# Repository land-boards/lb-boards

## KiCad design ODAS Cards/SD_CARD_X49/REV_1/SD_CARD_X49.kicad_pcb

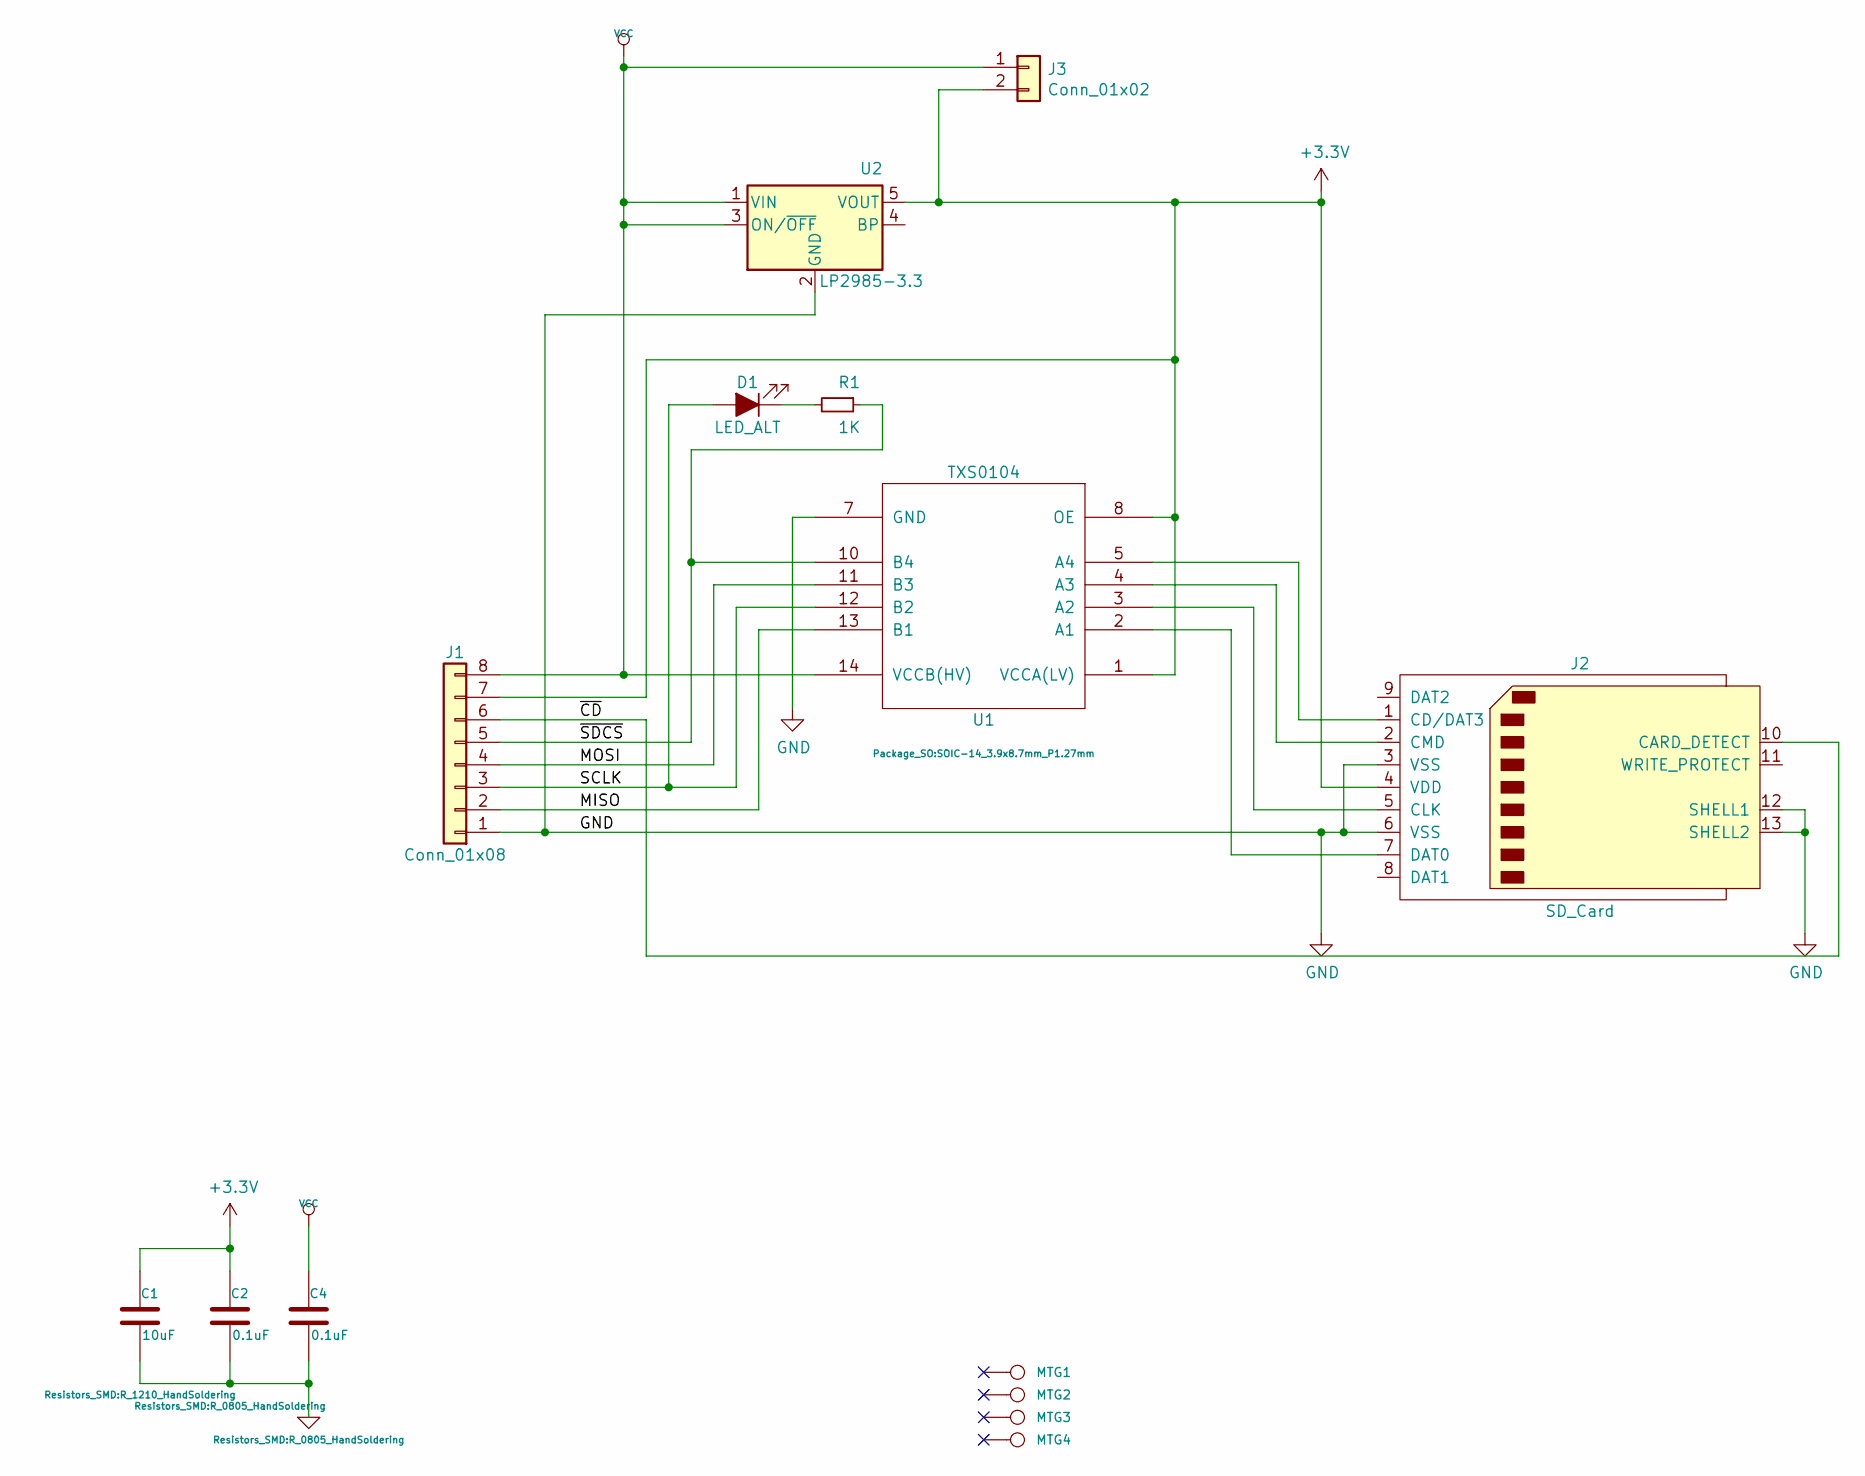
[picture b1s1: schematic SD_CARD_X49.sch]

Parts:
C1: 10uF; R_1210_HandSoldering
C2, C4: 0.1uF; R_0805_HandSoldering
D1: LED_ALT; LED_D3.0mm_Horizontal_O1.27mm_Z2.0mm_IRBlack
J1: Conn_01x08; PinHeader_1x08_P2.54mm_Horizontal
J2: SD_Card; SD_CARD
J3: Conn_01x02; PinHeader_1x02_P2.54mm_Horizontal
MTG1, MTG2, MTG3, MTG4: CONN_1; MTG-4-40
R1: 1K; R_0805_2012Metric_Pad1.15x1.40mm_HandSolder
U1: TXS0104; SOIC-14_3.9x8.7mm_P1.27mm
U2: LP2985-3.3; SOT-23-5

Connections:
+3V3: C1.1, C2.1, J1.7, J2.4 (VDD), J3.2, U1.1 (VCCA(LV)), U1.8 (OE), U2.5 (VOUT)
/MISO: J1.2, U1.13 (B1)
/MOSI: J1.4, U1.11 (B3)
/SCLK: D1.2 (A), J1.3, U1.12 (B2)
/~CD: J1.6, J2.10 (CARD_DETECT)
/~SDCS: J1.5, R1.1, U1.10 (B4)
GND: C1.2, C2.2, C4.2, J1.1, J2.3 (VSS), J2.6 (VSS), J2.12 (SHELL1), J2.13 (SHELL2), U1.7 (GND), U2.2 (GND)
unnamed: D1.1 (K), R1.2
unnamed: J2.1 (CD/DAT3), U1.5 (A4)
unnamed: J2.2 (CMD), U1.4 (A3)
unnamed: J2.5 (CLK), U1.3 (A2)
unnamed: J2.7 (DAT0), U1.2 (A1)
VCC: C4.1, J1.8, J3.1, U1.14 (VCCB(HV)), U2.1 (VIN), U2.3 (ON/~OFF~)

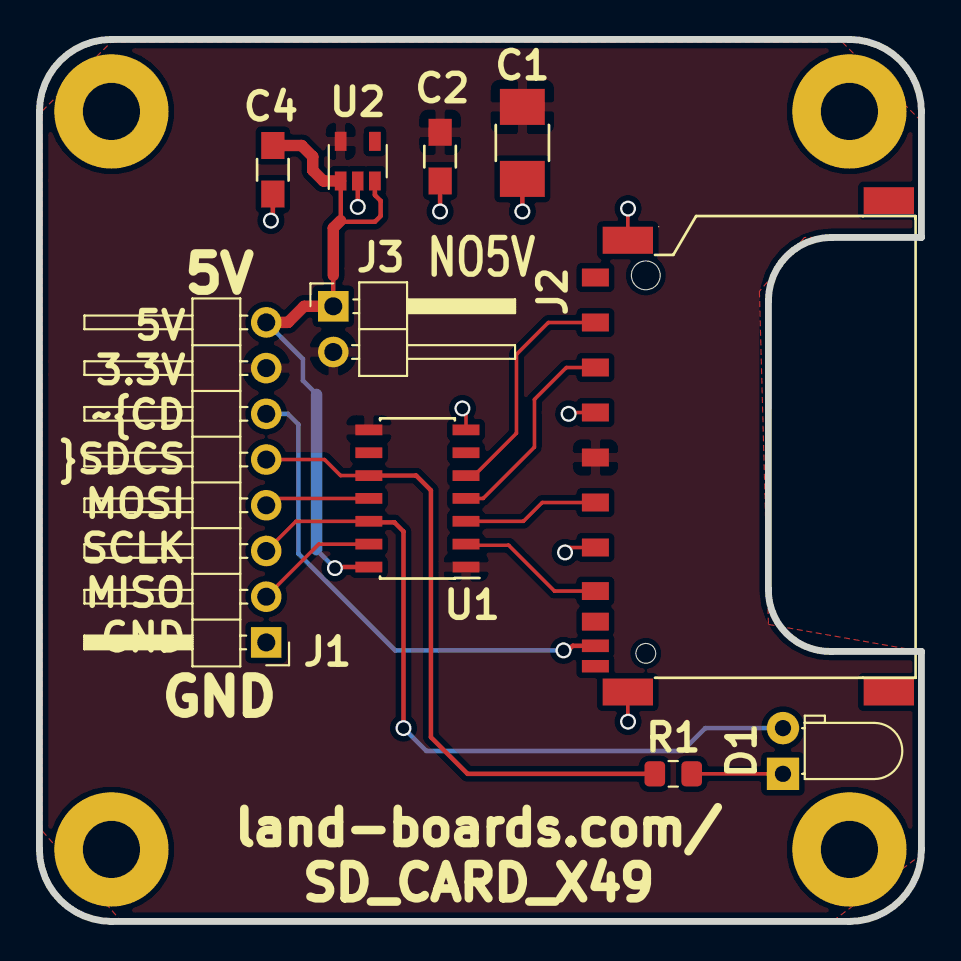
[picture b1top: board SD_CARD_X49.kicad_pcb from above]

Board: 2 copper layers, 49.0 x 49.0 mm, 14 parts (0 on the bottom side), 13 nets.

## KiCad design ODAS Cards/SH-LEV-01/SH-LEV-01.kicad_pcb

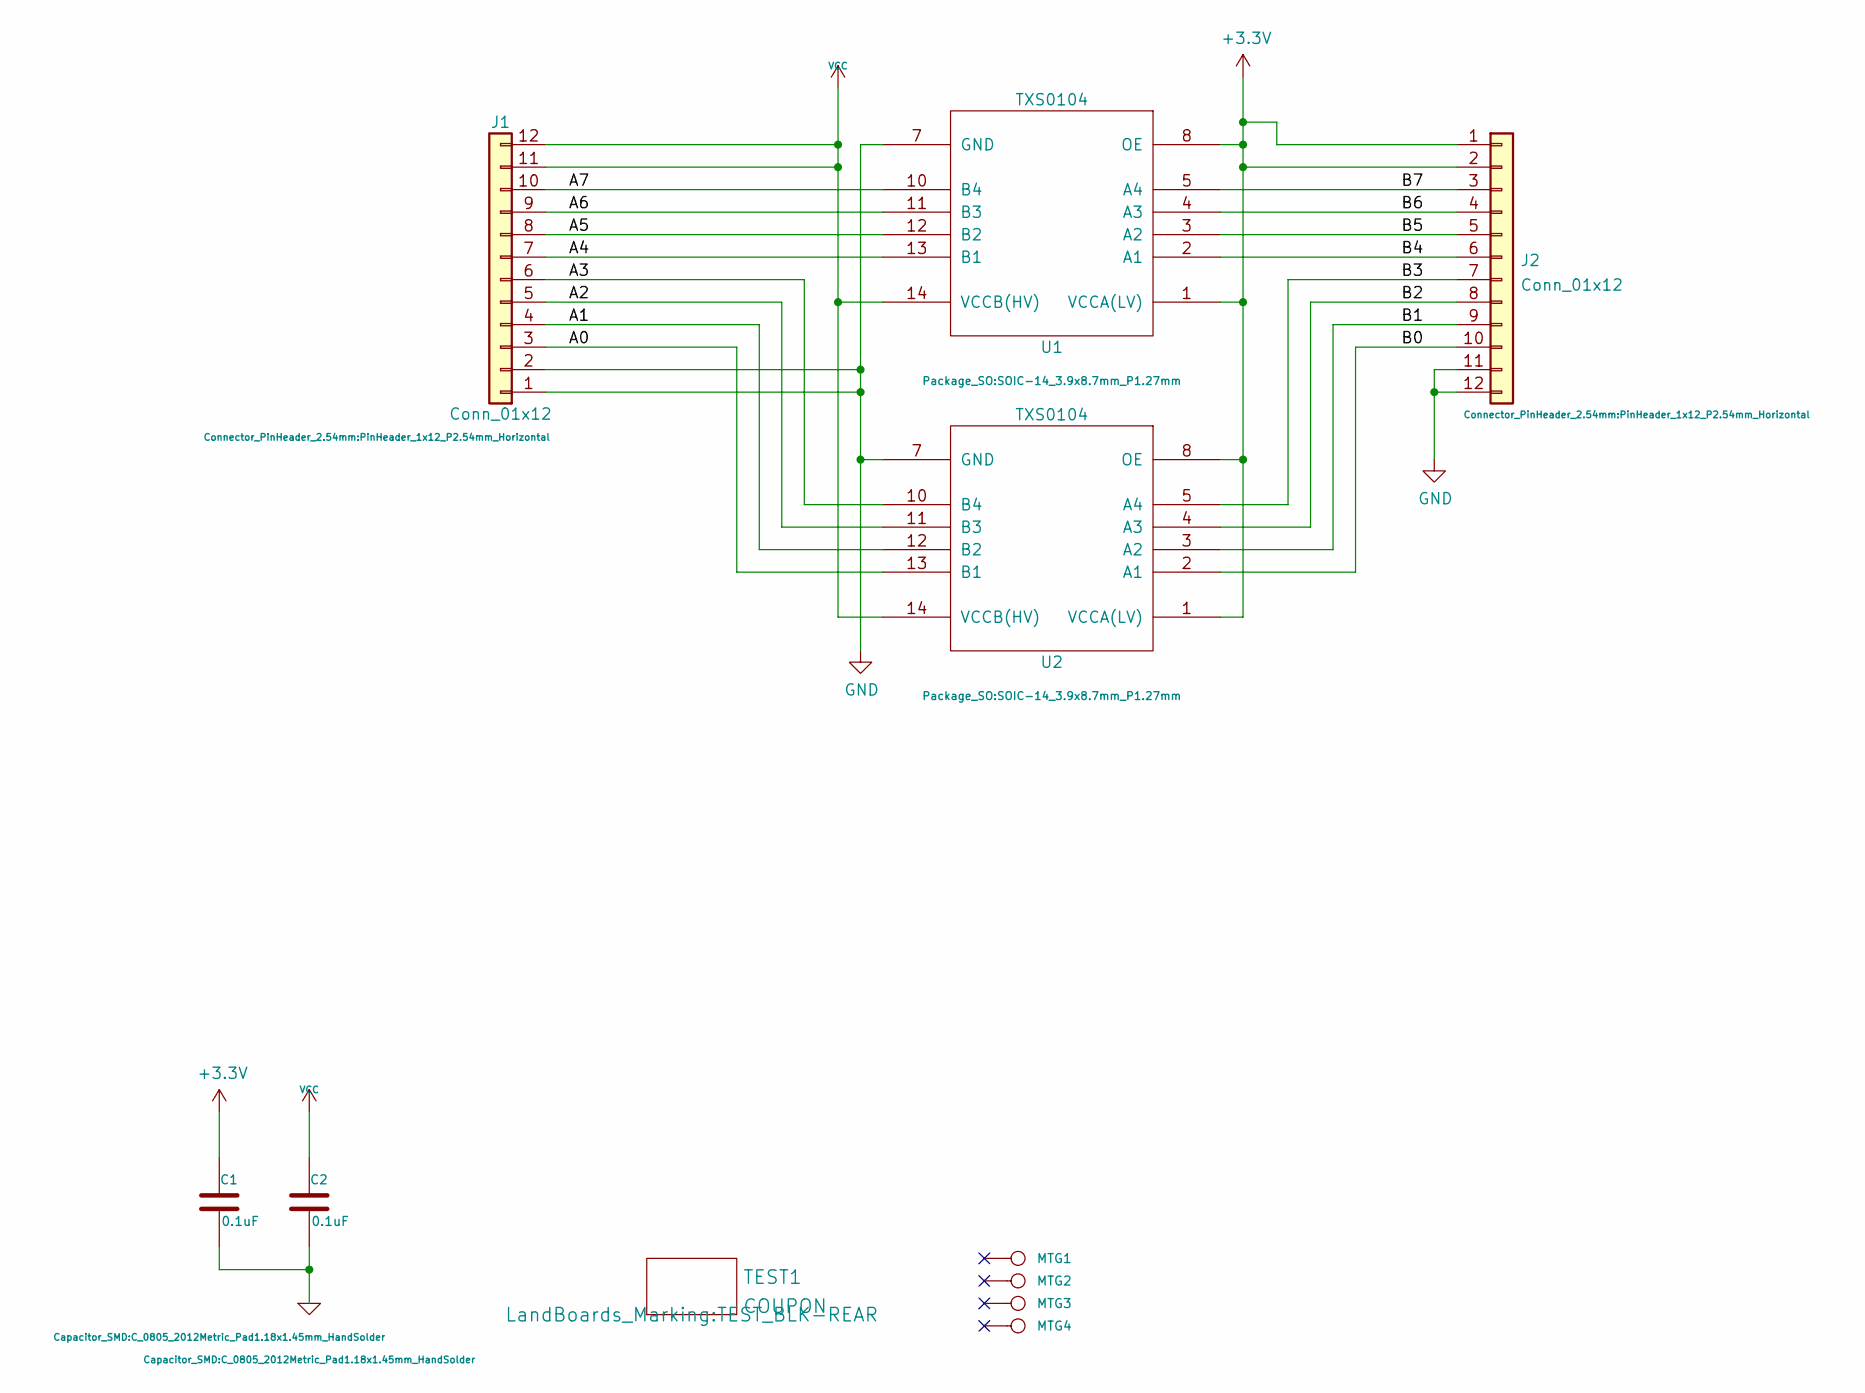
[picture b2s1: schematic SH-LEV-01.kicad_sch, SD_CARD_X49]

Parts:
C1, C2: 0.1uF; C_0805_2012Metric_Pad1.18x1.45mm_HandSolder
J1, J2: Conn_01x12; PinHeader_1x12_P2.54mm_Horizontal
MTG1, MTG2, MTG3, MTG4: CONN_1; MTG-4-40
TEST1: COUPON; TEST_BLK-REAR
U1, U2: TXS0104; SOIC-14_3.9x8.7mm_P1.27mm

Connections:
+3V3: C1.1, J2.1, J2.2, U1.1 (VCCA(LV)), U1.8 (OE), U2.1 (VCCA(LV)), U2.8 (OE)
/A0: J1.3, U2.13 (B1)
/A1: J1.4, U2.12 (B2)
/A2: J1.5, U2.11 (B3)
/A3: J1.6, U2.10 (B4)
/A4: J1.7, U1.13 (B1)
/A5: J1.8, U1.12 (B2)
/A6: J1.9, U1.11 (B3)
/A7: J1.10, U1.10 (B4)
/B0: J2.10, U2.2 (A1)
/B1: J2.9, U2.3 (A2)
/B2: J2.8, U2.4 (A3)
/B3: J2.7, U2.5 (A4)
/B4: J2.6, U1.2 (A1)
/B5: J2.5, U1.3 (A2)
/B6: J2.4, U1.4 (A3)
/B7: J2.3, U1.5 (A4)
GND: C1.2, C2.2, J1.1, J1.2, J2.11, J2.12, U1.7 (GND), U2.7 (GND)
VCC: C2.1, J1.11, J1.12, U1.14 (VCCB(HV)), U2.14 (VCCB(HV))

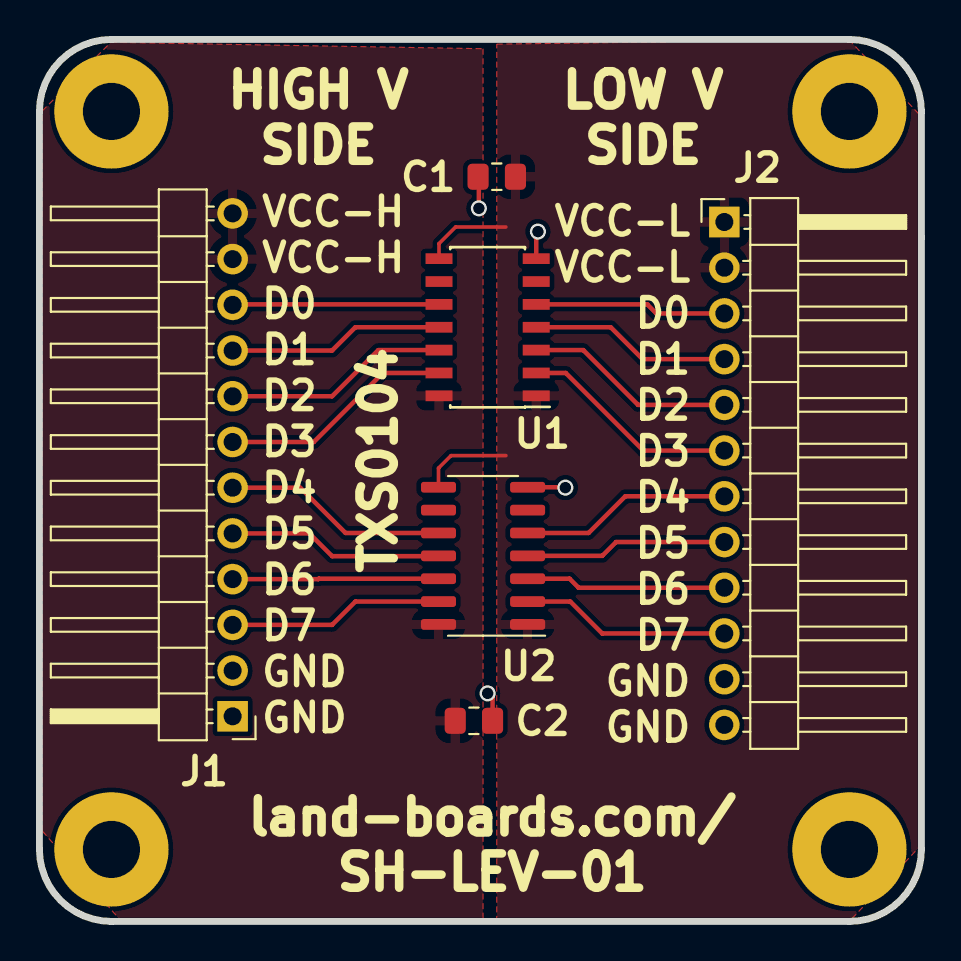
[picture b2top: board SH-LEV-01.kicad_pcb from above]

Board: 2 copper layers, 49.0 x 49.0 mm, 11 parts (0 on the bottom side), 19 nets.

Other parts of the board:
TEST: COUPON; TEST_BLK-REAR

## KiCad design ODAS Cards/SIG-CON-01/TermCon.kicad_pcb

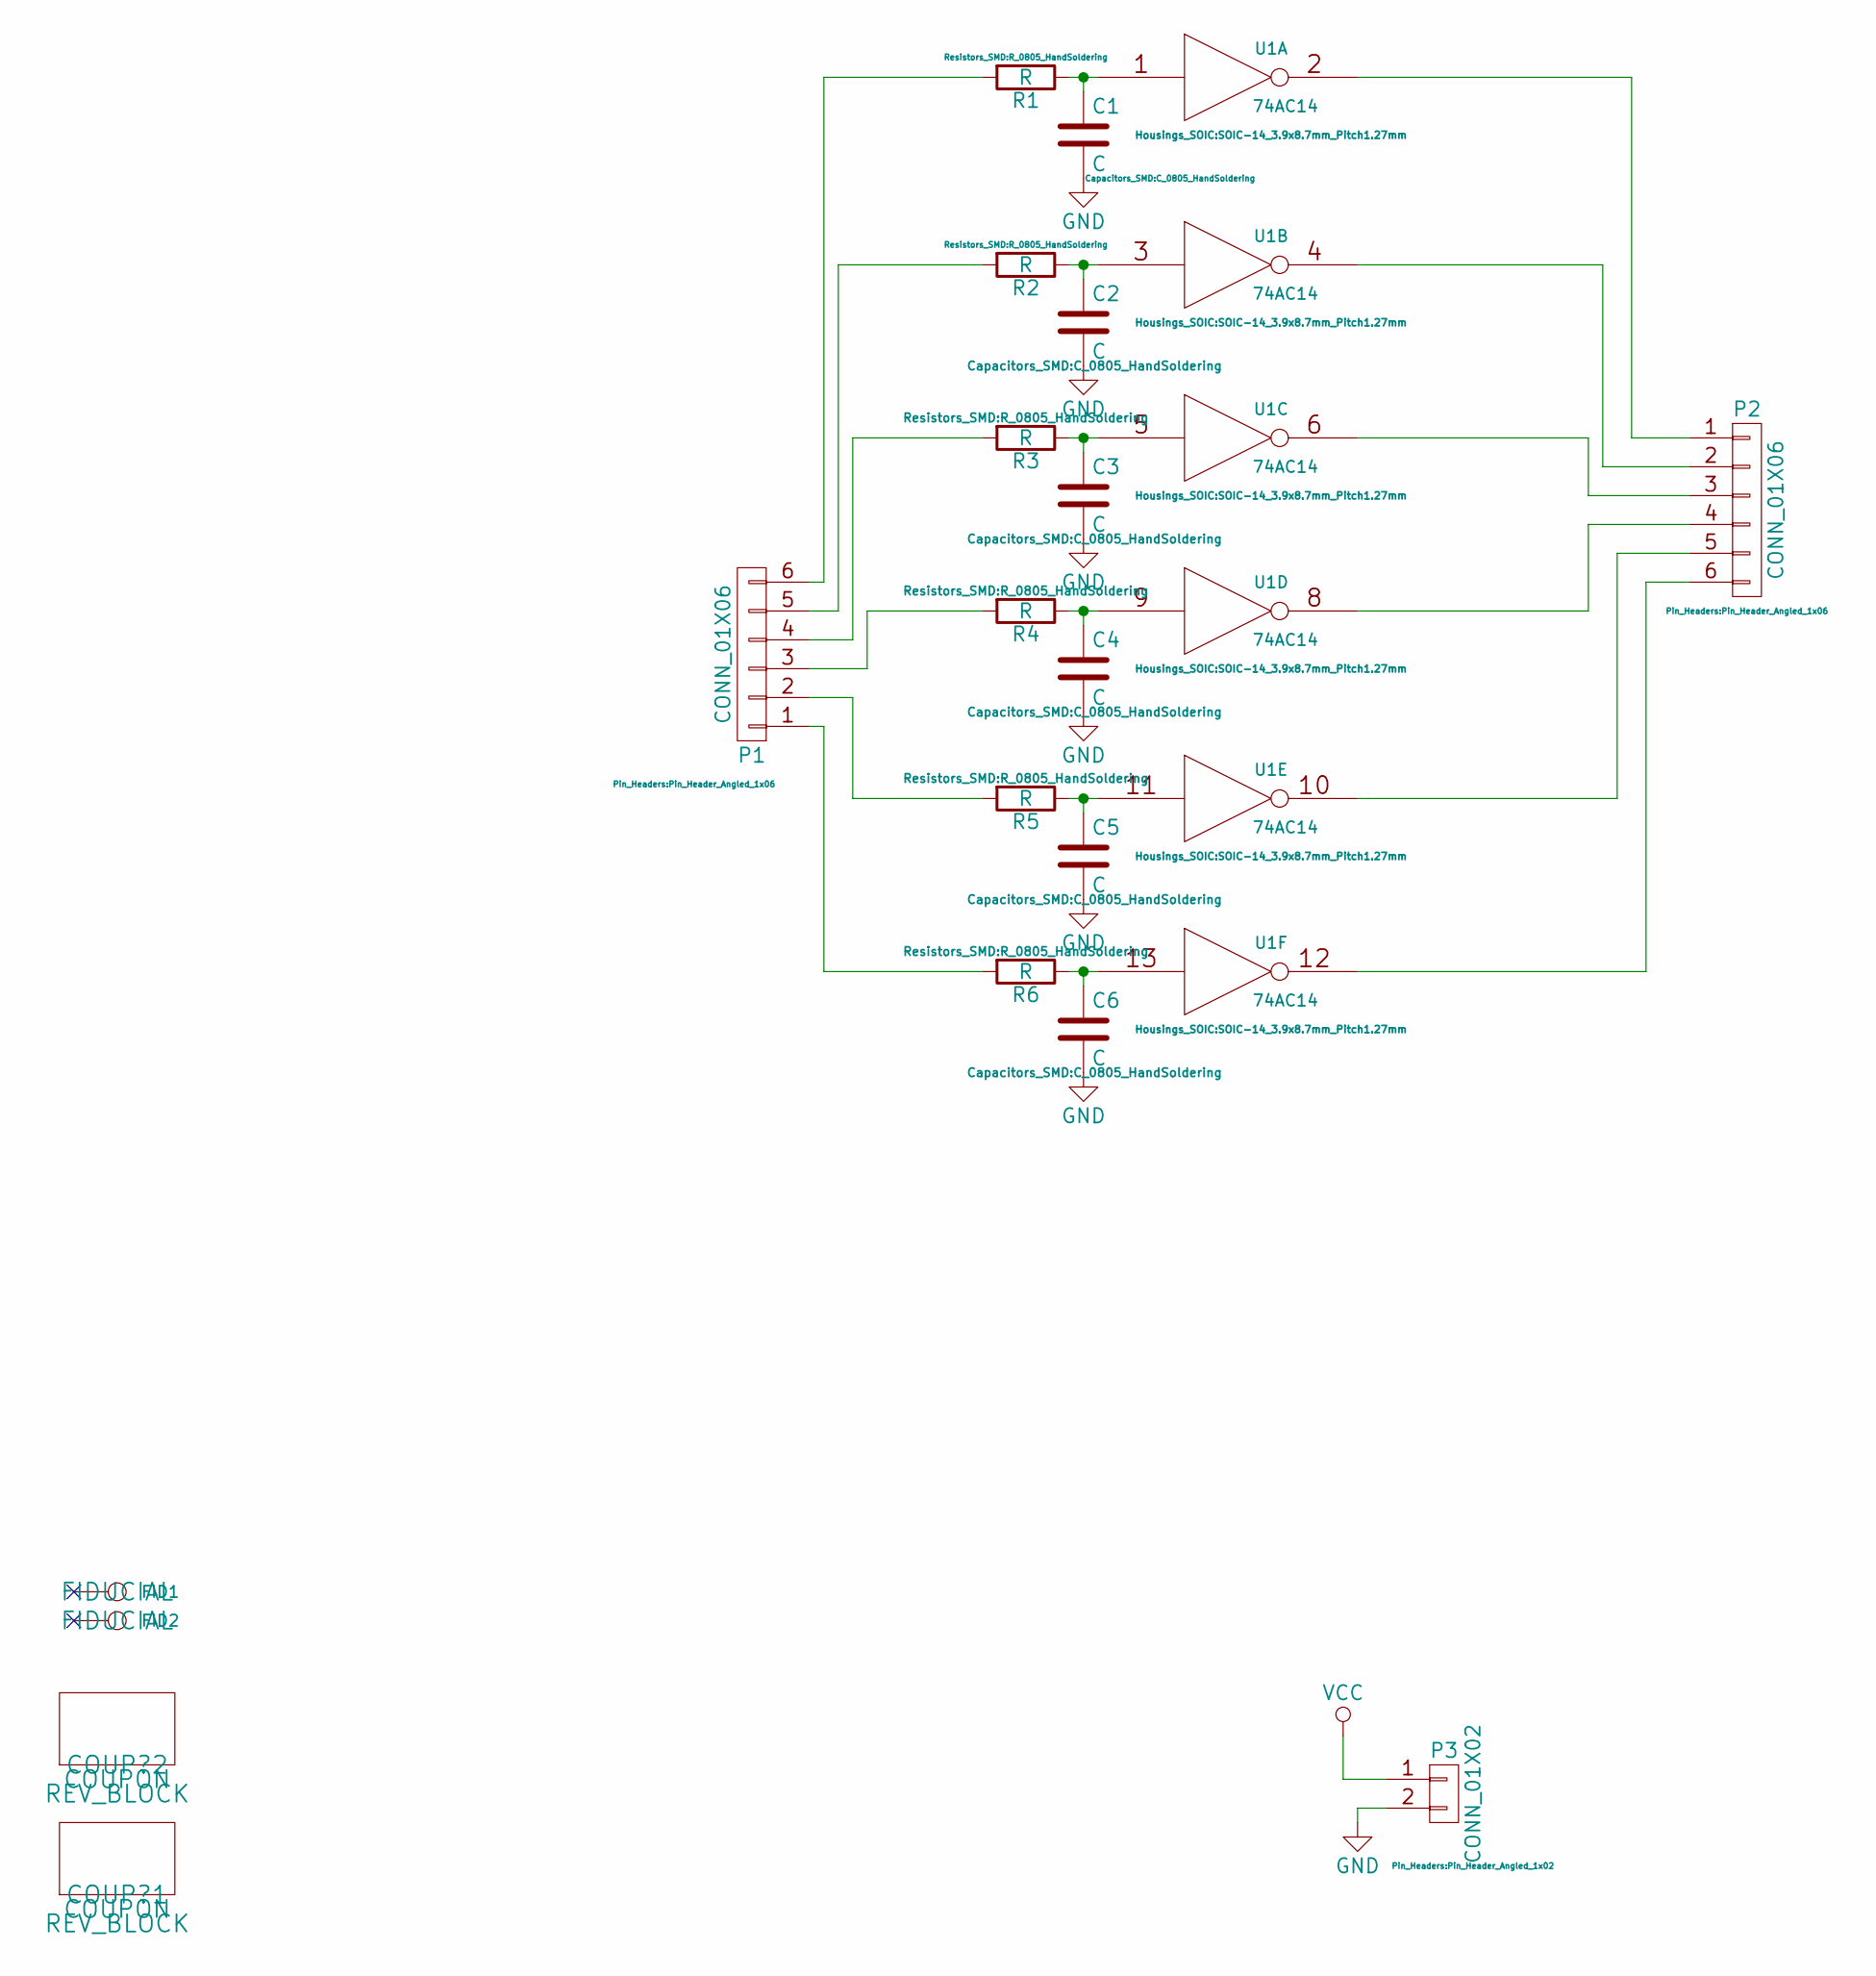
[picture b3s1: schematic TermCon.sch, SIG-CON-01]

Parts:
C1, C2, C3, C4, C5, C6: C; C_0805_HandSoldering
COUP?1, COUP?2: COUPON; REV_BLOCK
FID1, FID2: CONN_1; FIDUCIAL
P1, P2: CONN_01X06; Pin_Header_Angled_1x06
P3: CONN_01X02; Pin_Header_Angled_1x02
R1, R2, R3, R4, R5, R6: R; R_0805_HandSoldering
U1: 74AC14; SOIC-14_3.9x8.7mm_Pitch1.27mm

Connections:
GND: C1.2, C2.2, C3.2, C4.2, C5.2, C6.2, P3.2, U1.7 (GND)
unnamed: C1.1, R1.1, U1.1
unnamed: C2.1, R2.1, U1.3
unnamed: C3.1, R3.1, U1.5
unnamed: C4.1, R4.1, U1.9
unnamed: C5.1, R5.1, U1.11
unnamed: C6.1, R6.1, U1.13
unnamed: P1.1, R6.2
unnamed: P1.2, R5.2
unnamed: P1.3, R4.2
unnamed: P1.4, R3.2
unnamed: P1.5, R2.2
unnamed: P1.6, R1.2
unnamed: P2.1, U1.2
unnamed: P2.2, U1.4
unnamed: P2.3, U1.6
unnamed: P2.4, U1.8
unnamed: P2.5, U1.10
unnamed: P2.6, U1.12
VCC: P3.1, U1.14 (VCC)

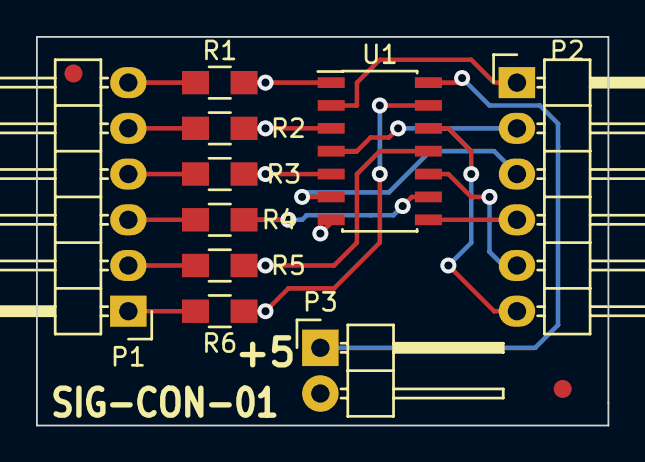
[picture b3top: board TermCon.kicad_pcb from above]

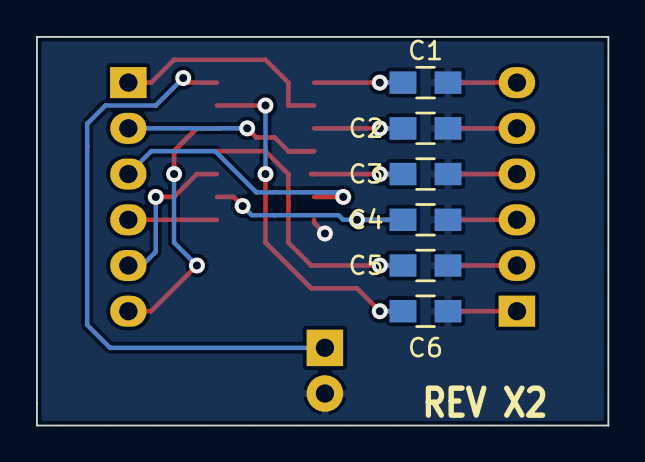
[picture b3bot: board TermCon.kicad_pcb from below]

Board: 2 copper layers, 31.8 x 21.6 mm, 18 parts (6 on the bottom side), 20 nets.

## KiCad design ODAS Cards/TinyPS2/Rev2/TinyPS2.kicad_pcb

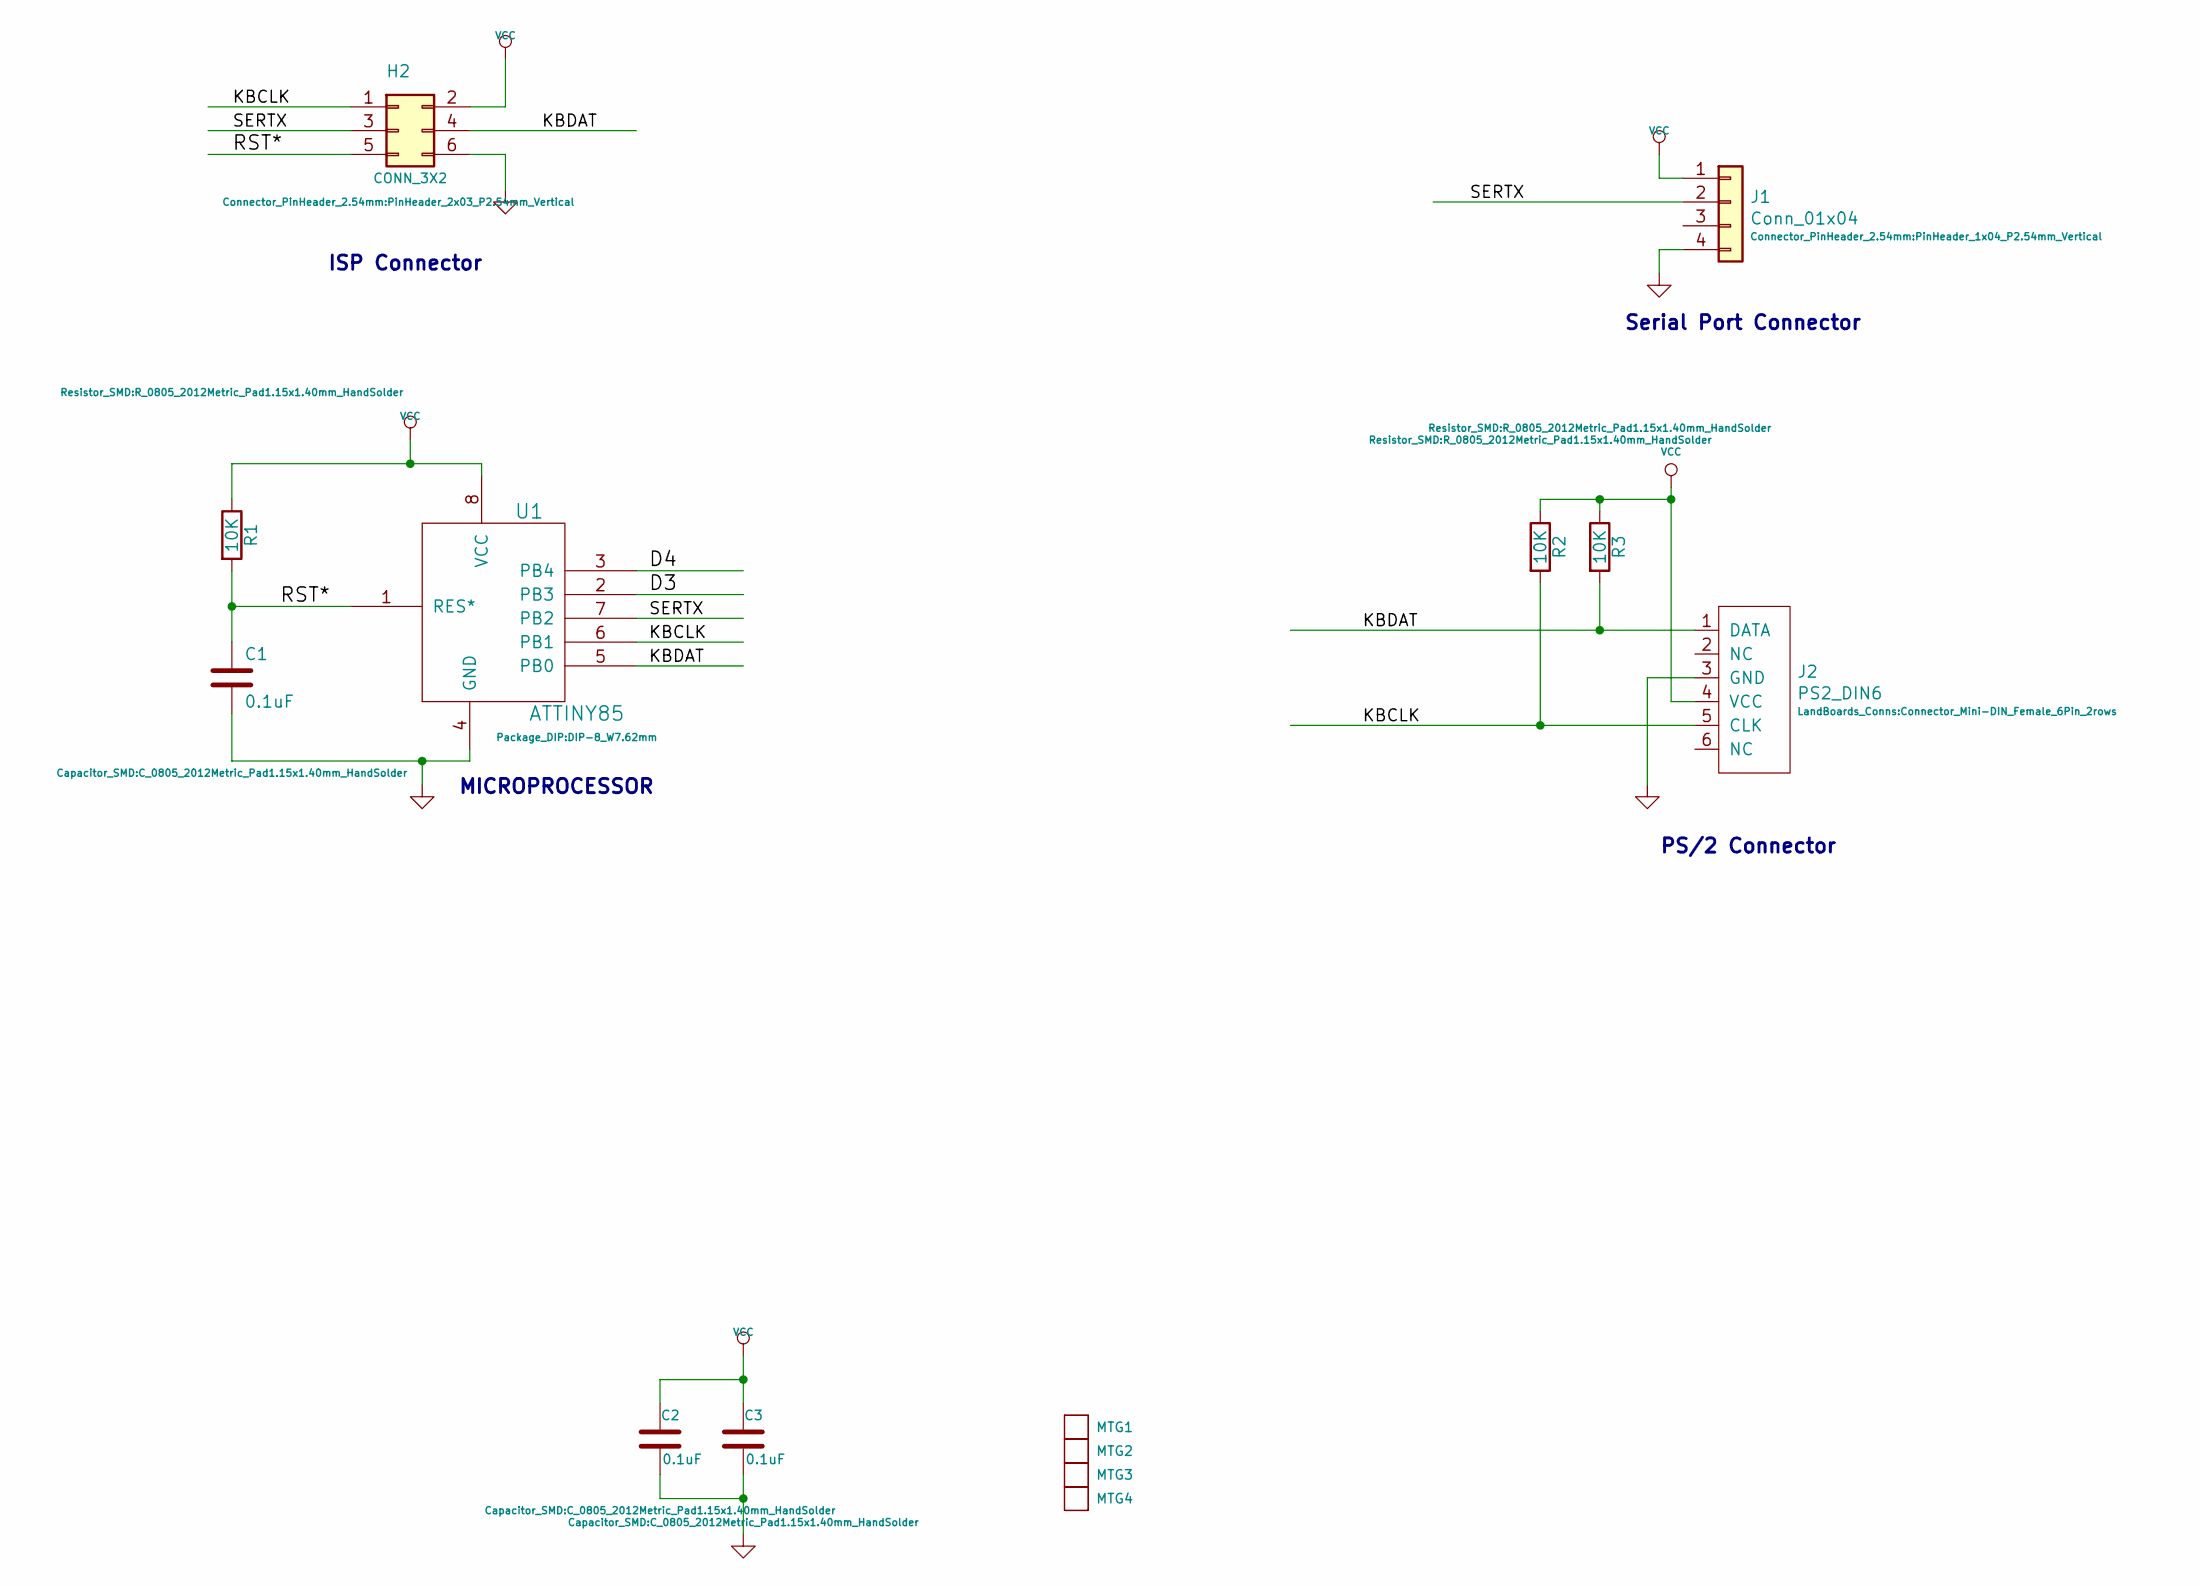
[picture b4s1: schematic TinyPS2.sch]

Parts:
C1, C2, C3: 0.1uF; C_0805_2012Metric_Pad1.15x1.40mm_HandSolder
H2: CONN_3X2; PinHeader_2x03_P2.54mm_Vertical
J1: Conn_01x04; PinHeader_1x04_P2.54mm_Vertical
J2: PS2_DIN6; Connector_Mini-DIN_Female_6Pin_2rows
MTG1, MTG2, MTG3, MTG4: CONN_1; MTG-4-40
R1, R2, R3: 10K; R_0805_2012Metric_Pad1.15x1.40mm_HandSolder
U1: ATTINY85; DIP-8_W7.62mm

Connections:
/D3: U1.2 (PB3)
/D4: U1.3 (PB4)
/KBCLK: H2.1, J2.5 (CLK), R2.2, U1.6 (PB1)
/KBDAT: H2.4, J2.1 (DATA), R3.2, U1.5 (PB0)
/RST*: C1.1, H2.5, R1.2, U1.1 (RES*)
/SERTX: H2.3, J1.2, U1.7 (PB2)
GND: C1.2, C2.2, C3.2, H2.6, J1.4, J2.3 (GND), U1.4 (GND)
VCC: C2.1, C3.1, H2.2, J1.1, J2.4 (VCC), R1.1, R2.1, R3.1, U1.8 (VCC)

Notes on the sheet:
MICROPROCESSOR
ISP Connector
PS/2 Connector
Serial Port Connector

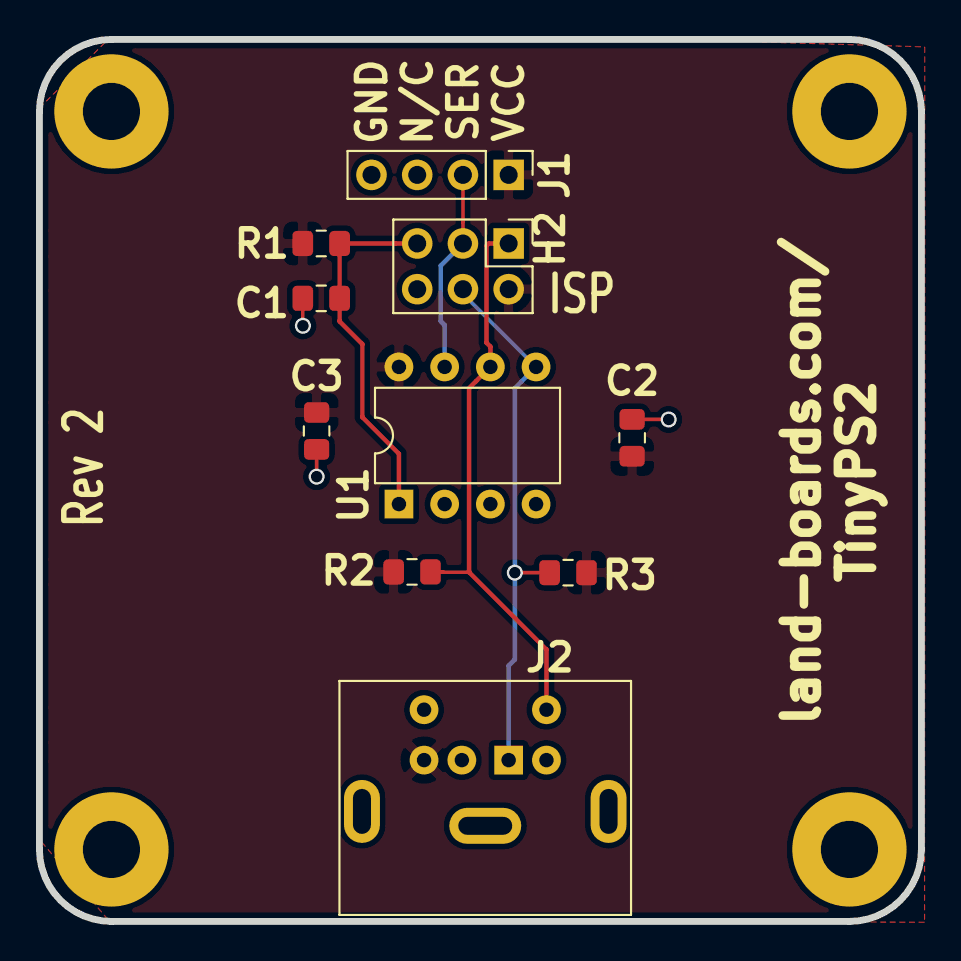
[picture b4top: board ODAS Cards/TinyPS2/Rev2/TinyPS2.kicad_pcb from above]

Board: 2 copper layers, 49.0 x 49.0 mm, 14 parts (0 on the bottom side), 6 nets.

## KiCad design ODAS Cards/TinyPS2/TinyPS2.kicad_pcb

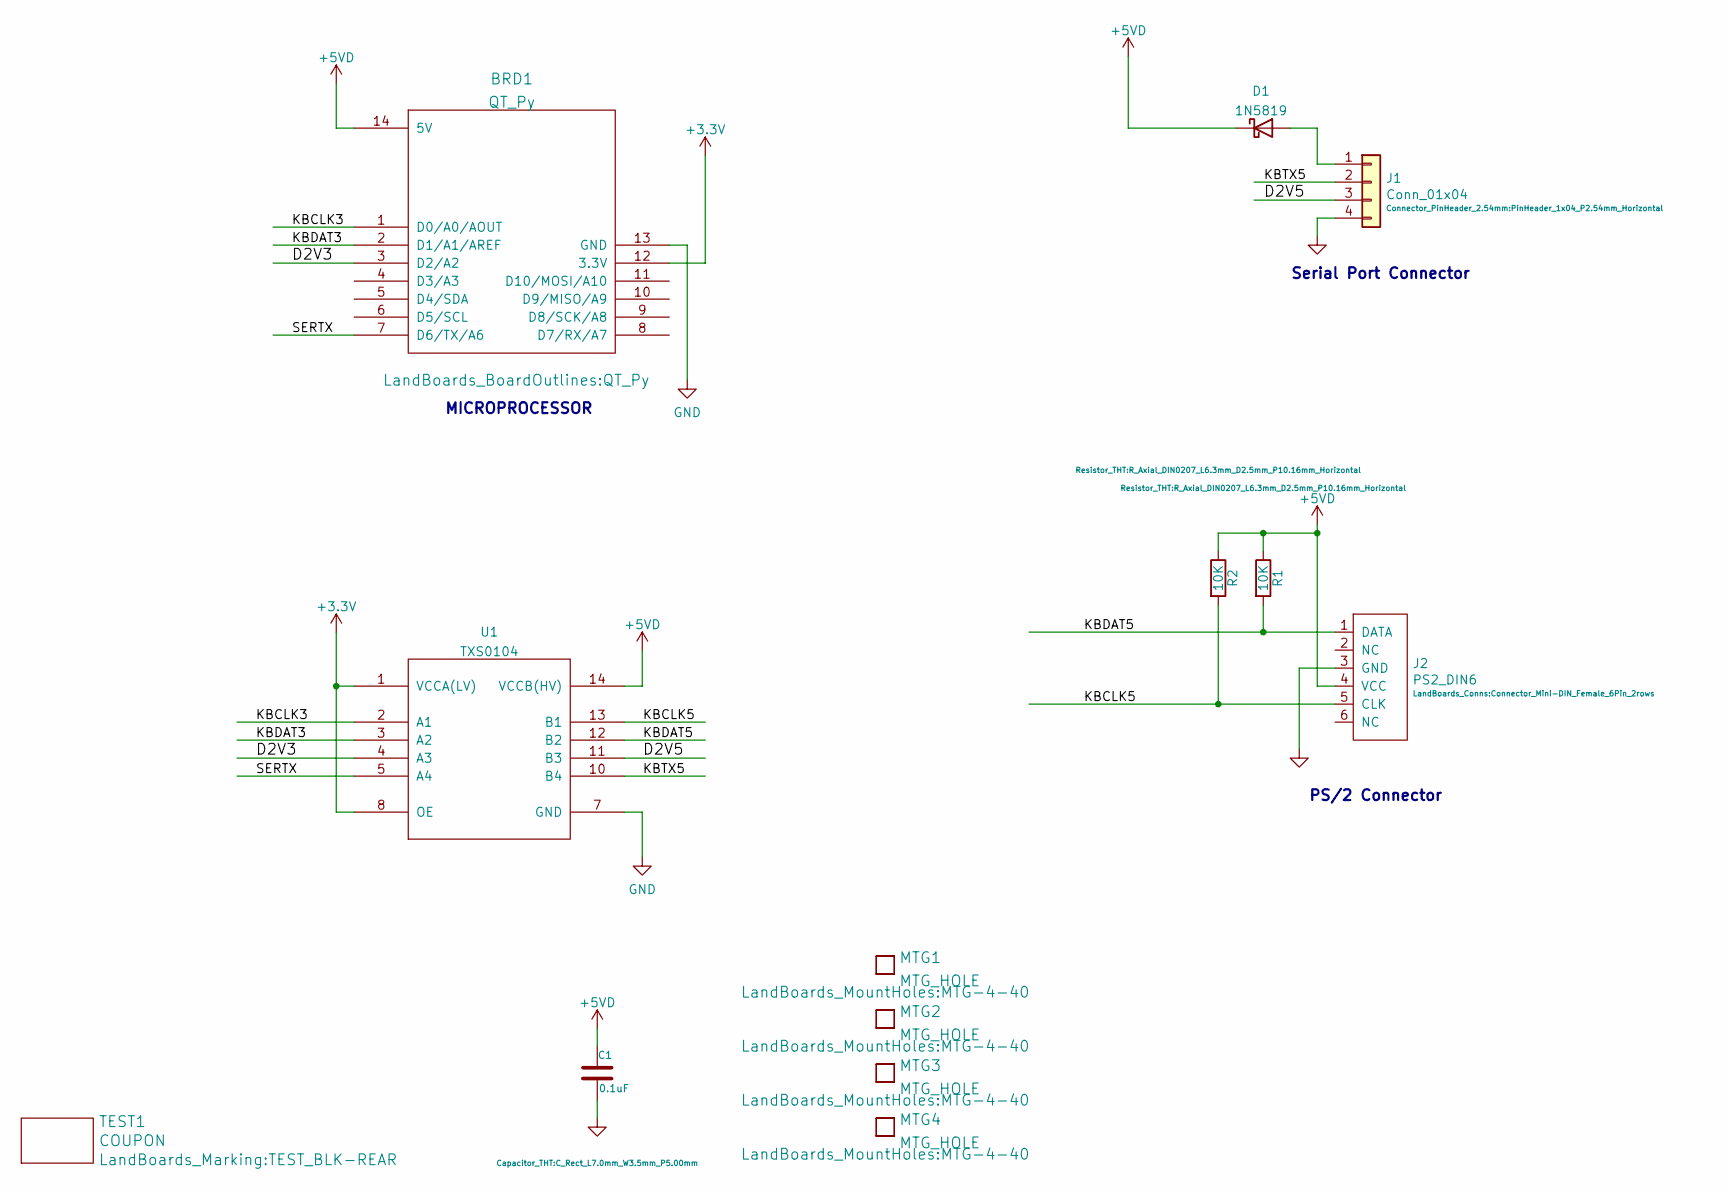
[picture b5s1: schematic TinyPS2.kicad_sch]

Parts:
BRD1: QT_Py
C1: 0.1uF; C_Rect_L7.0mm_W3.5mm_P5.00mm
D1: 1N5819; D_DO-41_SOD81_P10.16mm_Horizontal
J1: Conn_01x04; PinHeader_1x04_P2.54mm_Horizontal
J2: PS2_DIN6; Connector_Mini-DIN_Female_6Pin_2rows
MTG1, MTG2, MTG3, MTG4: MTG_HOLE; MTG-4-40
R1, R2: 10K; R_Axial_DIN0207_L6.3mm_D2.5mm_P10.16mm_Horizontal
TEST1: COUPON; TEST_BLK-REAR
U1: TXS0104; SO-14_3.9x8.65mm_P1.27mm

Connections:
+3V3: BRD1.12 (3.3V), U1.1 (VCCA(LV)), U1.8 (OE)
+5VD: BRD1.14 (5V), C1.1, D1.1 (K), J2.4 (VCC), R1.1, R2.1, U1.14 (VCCB(HV))
/D2V3: BRD1.3 (D2/A2), U1.4 (A3)
/D2V5: J1.3, U1.11 (B3)
/KBCLK3: BRD1.1 (D0/A0/AOUT), U1.2 (A1)
/KBCLK5: J2.5 (CLK), R2.2, U1.13 (B1)
/KBDAT3: BRD1.2 (D1/A1/AREF), U1.3 (A2)
/KBDAT5: J2.1 (DATA), R1.2, U1.12 (B2)
/KBTX5: J1.2, U1.10 (B4)
/SERTX: BRD1.7 (D6/TX/A6), U1.5 (A4)
GND: BRD1.13 (GND), C1.2, J1.4, J2.3 (GND), U1.7 (GND)
unnamed: D1.2 (A), J1.1

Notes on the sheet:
Serial Port Connector
PS/2 Connector
MICROPROCESSOR

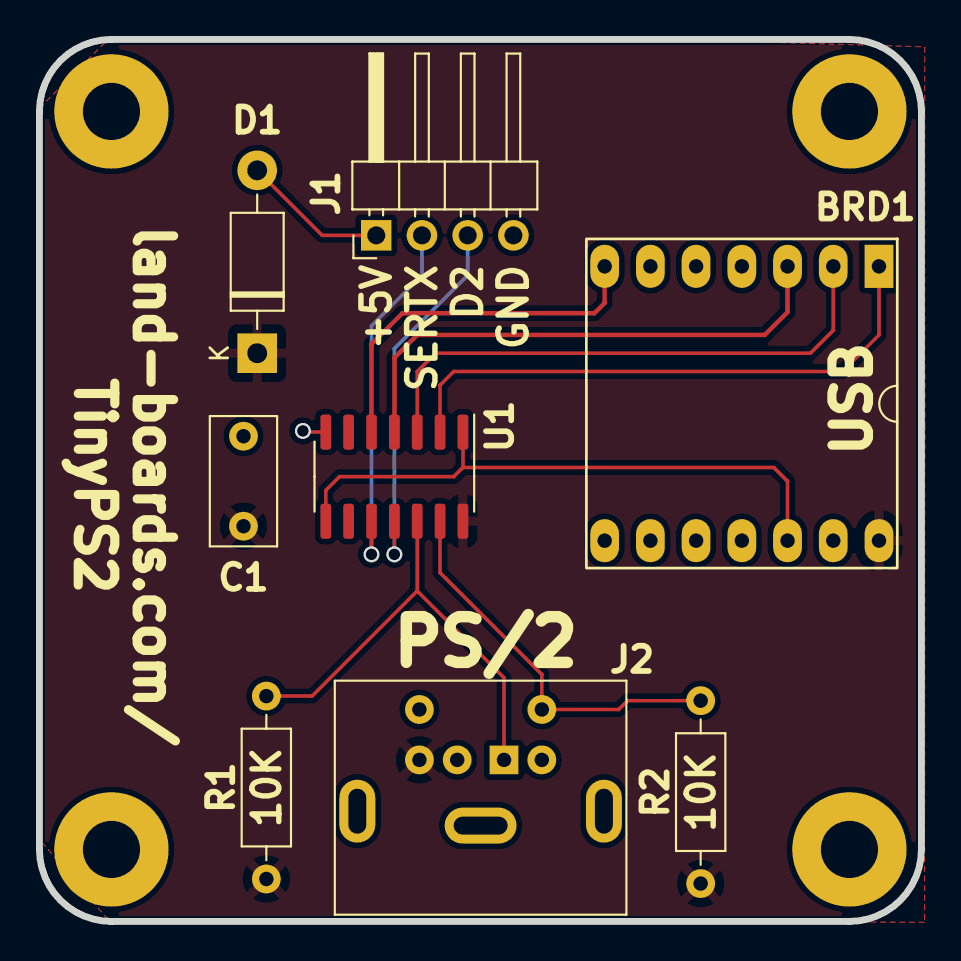
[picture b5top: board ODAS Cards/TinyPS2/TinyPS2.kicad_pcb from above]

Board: 2 copper layers, 49.0 x 49.0 mm, 13 parts (0 on the bottom side), 12 nets.

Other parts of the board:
TEST: COUPON; TEST_BLK-REAR
